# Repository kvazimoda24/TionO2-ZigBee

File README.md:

## README.md
Проект для подключения бризера Tion O2 к умному дому через протокол ZigBee

Отлаживалось на бризерах выпущенных в октябре 2020 года. На экземплярах выпущенных раньше или позже может использоваться другой дисплей или другая прошивка.

В бризере в качестве контроллера ЖК дисплея используется микросхема HOLTEK HT1622.<br>
Основная идея заключается в том, что мы цепляемся паралельно входу этой микросхемы и снифим данные, отправляемые в неё.<br>
Для управления замыкаем выводы кнопок панели управления бризера имитируя, таким образом, нажатия на них.<br>

Ядром проекта является микроконтроллер **ATmega328P**.<br>
Для работы по протоколу ZigBee используется модуль **E18-MS1-PCB**. Так же пробовал модуль **E18-MS1PA1-PCB**, но из-за встроенного усилителя он слишком много потребляет, и его не вытягивает встроенный блок питания бризера.

### Статус
При изменениях температуры или режима работы бризера, а также примерно каждые 20 минут на координатор отправляется текущий статус бризера.<br>
Посылка представляет JSON вида: `{"PWR":"1","APW":"1","OUT":"5","SPD":"3","HTE":"1","TMS":"0","HTT":"18"}`<br>
Параметры:<br>
**PWR** - работает бризер или в режиме standbuy (0 - standbuy, 1 - работает)<br>
**APW** - включён ли режим автоматического включения после сбоя питания. Если 1, то после подачи питания, если на момент сбоя бризер был включён, то бризер включится.<br>
**OUT** - температура входящего воздуха<br>
**SPD** - скорость работы вентилятора (от 1 до 4)<br>
**HTE** - включён ли подогрев воздуха<br>
**HTT** - до какой температуры подогревается входящий воздух<br>
**FLT** - осталось дней до замены фильтров<br>
**MNT** - минимально допустимая температура входящего воздуха<br>
**TIM** - текущее время (формат ЧЧММ)<br>
**TMS** - включён ли таймер включения/выключения<br>
**TME** - время включения (формат ЧЧММ)<br>
**TMD** - время выключения (формат ЧЧММ)<br>
**ERROR** - в случае, если бризер отобразил ошибку, то будет отправлен только этот параметр, в значении будет строка с ошибкой. Так же, в случае, если не удалось распознать данные на дисплее, то в значении будет пусто.

### Управление
Для управления необходимо отправить строку, содержащую одну или несколько команд.<br>
Строка состоит из названия параметра, разделителя, значения параметра. Разделителем является двоеточие ":".<br>
Можно отправить разом несколько параметров. В этом случае параметры должны отделаться друг от друга запятой ","<br>
Оканчиваться строка должна символом возврата каретки (код символа 0x0D).<br>
Максимальная длинна строки 127 символов.<br>
Параметры будут применяться в том же порядке, что и в отправленной команде.<br>
Если встречается ошибочный параметр, то дальнейший разбор строки прекращается.<br>

Пример строки: `PWR:1,SPD:2,HTE:1,HTT:17\r`

Сами параметры аналогичны тем, что перечислены в статусе, за исключением параметра FLT - изменение срока замены фильтров я не реализовывал, т.к. не увидел необходимости в этом.<br>
Так же, добавлена дополнительная команда EXS. Значение можно выставить любое число до 4 знаков, например 1.<br>
При получении этой команды контроллер проходит по всем настройкам бризера и отправляет их координатору ZigBee сети. Это нужно, чтобы получить текущие значения таймеров, текущего времени, срока службы фильтров и минимально допустимой температуры.<br>

На стороне координатора я использую проект zigbee2mqtt. В нём статус можно получить по адресу *zigbee2mqtt/device_id/action*
Строка с командами же отправляется по адресу *zigbee2mqtt/device_id/set/action* содержимое `PWR:1,SPD:2,HTE:1,HTT:17`

### Каталоги и файлы
**arduino** - проект в Arduino IDE версии 1.8.16 - сдесь код для контроллера ATmega328P<br>
**kicad** - проект в kiCAD версии 5.0.2 - схема платы, печатная плата и готовые герберы.<br>
**CC2530** - прошивки для ZigBee модулей<br>
**TION-O2_ZIGBEE.js** - файл описания устройства для zigbee2mqtt. Его надо положить в каталог data проекта zigbee2mqtt и прописать в файле configuration.yaml:
```
external_converters:
  - TION-O2_ZIGBEE.js
```
Прошивка для ZigBee модуля создана с помощью контруктора прошивок с сайта https://ptvo.info<br>
Вдохновлялся проектом https://hackaday.io/project/168959-let-me-control-you-hitachi-air-conditioner<br>

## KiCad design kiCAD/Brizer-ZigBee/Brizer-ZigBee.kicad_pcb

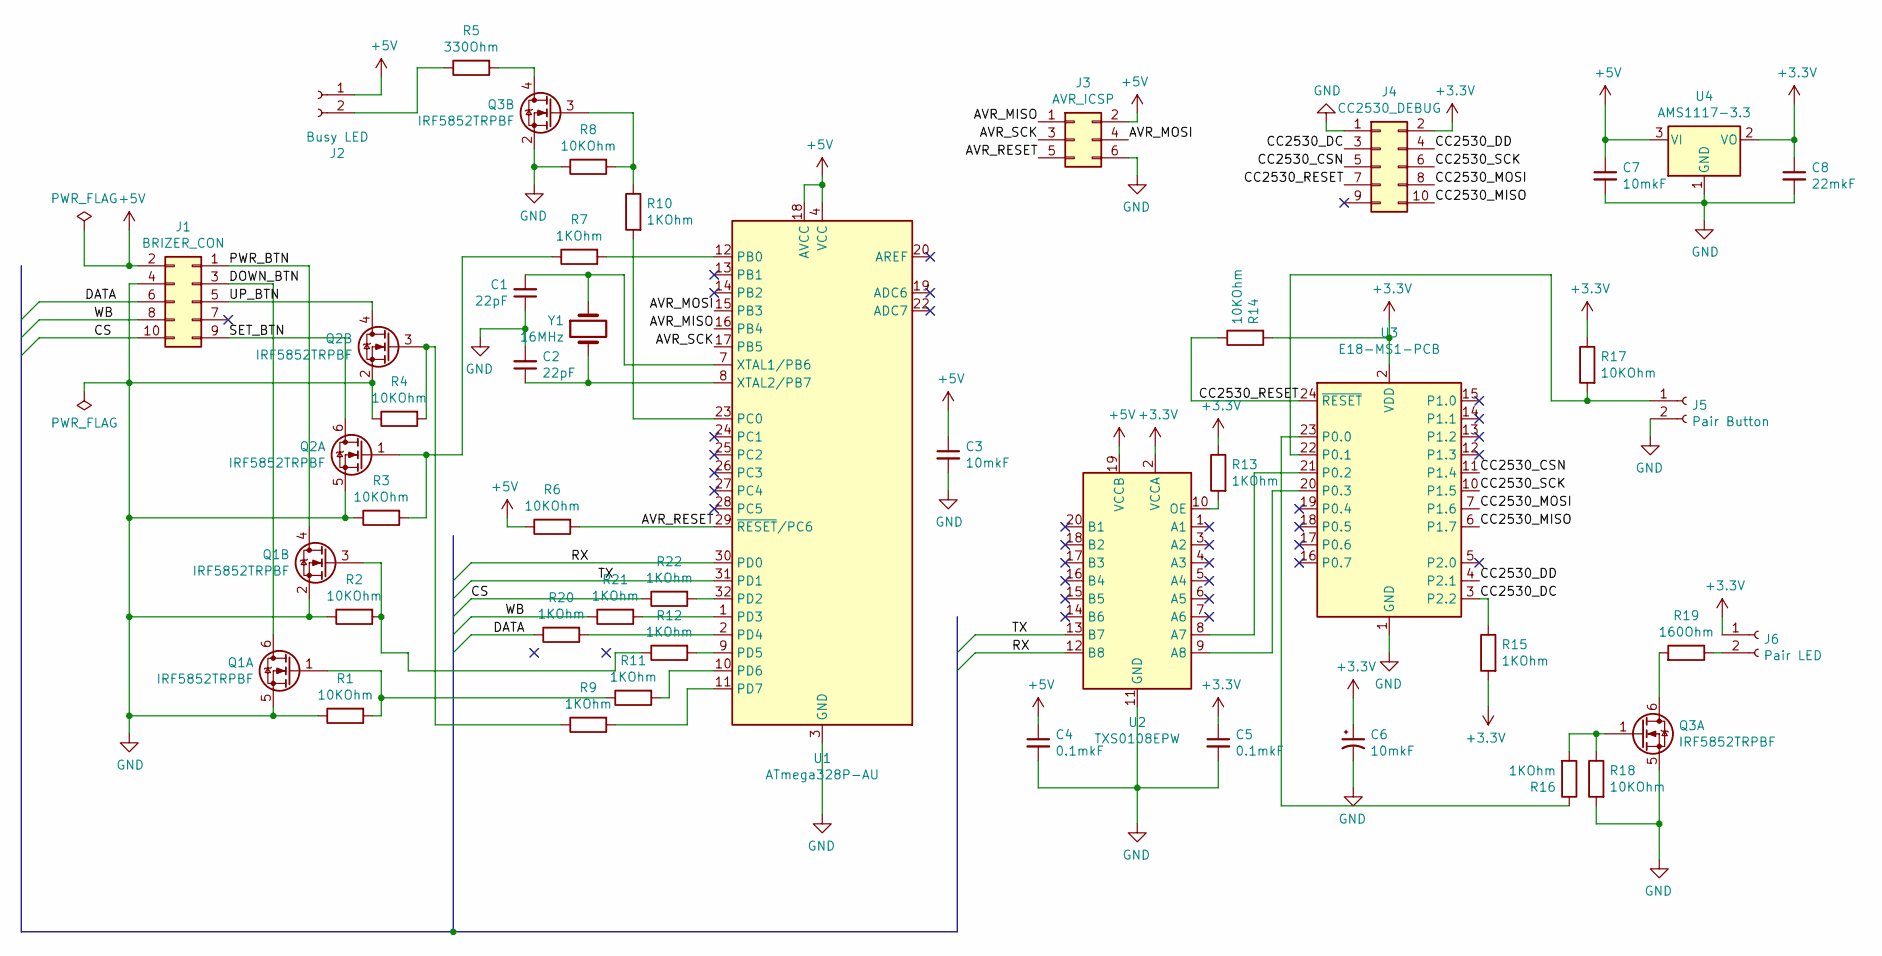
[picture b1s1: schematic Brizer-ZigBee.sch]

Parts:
C1, C2: 22pF; C_0805_2012Metric
C3, C7: 10mkF; C_0805_2012Metric
C4, C5: 0.1mkF; C_1206_3216Metric
C6: 10mkF; CP_EIA-3528-21_Kemet-B
C8: 22mkF; C_0805_2012Metric
J1: BRIZER_CON; IDC-Header_2x05_P2mm_Vertical
J2: Busy LED; PinHeader_1x02_P2.54mm_Vertical
J3: AVR_ICSP; PinHeader_2x03_P2.00mm_Vertical
J4: CC2530_DEBUG; PinHeader_2x05_P2.00mm_Vertical
J5: Pair Button; PinHeader_1x02_P2.54mm_Vertical
J6: Pair LED; PinHeader_1x02_P2.54mm_Vertical
Q1, Q2, Q3: IRF5852TRPBF; TSOP-6_1.65x3.05mm_P0.95mm
R1, R2, R3, R4, R6, R8, R14, R17, R18: 10KOhm; R_0805_2012Metric
R5: 330Ohm; R_0805_2012Metric
R7, R9, R10, R11, R12, R13, R15, R16, R20, R21, R22: 1KOhm; R_0805_2012Metric
R19: 160Ohm; R_0805_2012Metric
U1: ATmega328P-AU; TQFP-32_7x7mm_P0.8mm
U2: TXS0108EPW; TSSOP-20_4.4x6.5mm_P0.65mm
U3: E18-MS1-PCB; E18-MS1PA1-PCB
U4: AMS1117-3.3; SOT-223-3_TabPin2
Y1: 16MHz; Crystal_SMD_HC49-SD

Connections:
+3V3: C5.1, C6.1, C8.1, J4.2, J6.1, R13.1, R14.2, R15.2, R17.1, U2.2 (VCCA), U3.2 (VDD), U4.2 (VO)
+5V: C3.1, C4.1, C7.1, J1.2, J2.1, J3.2, R6.1, U1.4 (VCC), U1.6 (VCC), U1.18 (AVCC), U2.19 (VCCB), U4.3 (VI)
/AVR_MISO: J3.1, U1.16 (PB4)
/AVR_MOSI: J3.4, U1.15 (PB3)
/AVR_RESET: J3.5, R6.2, U1.29 (~RESET~/PC6)
/AVR_SCK: J3.3, U1.17 (PB5)
/CC2530_CSN: J4.5, U3.11 (P1.4)
/CC2530_DC: J4.3, R15.1, U3.3 (P2.2)
/CC2530_DD: J4.4, U3.4 (P2.1)
/CC2530_MISO: J4.10, U3.6 (P1.7)
/CC2530_MOSI: J4.8, U3.7 (P1.6)
/CC2530_RESET: J4.7, R14.1, U3.24 (~RESET)
/CC2530_SCK: J4.6, U3.10 (P1.5)
/CS: J1.10, R22.1
/DATA: J1.6, R20.1
/DOWN_BTN: J1.3, Q1.6 (D)
/PWR_BTN: J1.1, Q1.4 (D)
/RX: U1.30 (PD0), U2.12 (B8)
/SET_BTN: J1.9, Q2.6 (D)
/TX: U1.31 (PD1), U2.13 (B7)
/UP_BTN: J1.5, Q2.4 (D)
/WB: J1.8, R21.1
GND: C1.1, C2.2, C3.2, C4.2, C5.2, C6.2, C7.2, C8.2, J1.4, J3.6, J4.1, J5.2, Q1.2 (S), Q1.5 (S), Q2.2 (S), Q2.5 (S), Q3.2 (S), Q3.5 (S), R1.1, R2.1, R3.1, R4.1, R8.1, R18.2, U1.3 (GND), U1.5 (GND), U1.21 (GND), U2.11 (GND), U3.1 (GND), U4.1 (GND)
unnamed: C1.2, U1.7 (XTAL1/PB6), Y1.1
unnamed: C2.1, U1.8 (XTAL2/PB7), Y1.2
unnamed: J2.2, R5.1
unnamed: J5.1, R17.2, U3.22 (P0.1)
unnamed: J6.2, R19.1
unnamed: Q1.1 (G), R1.2, R11.1
unnamed: Q1.3 (G), R2.2, R12.1
unnamed: Q2.1 (G), R3.2, R7.1
unnamed: Q2.3 (G), R4.2, R9.1
unnamed: Q3.1 (G), R16.2, R18.1
unnamed: Q3.3 (G), R8.2, R10.1
unnamed: Q3.4 (D), R5.2
unnamed: Q3.6 (D), R19.2
unnamed: R7.2, U1.12 (PB0)
unnamed: R9.2, U1.11 (PD7)
unnamed: R10.2, U1.23 (PC0)
unnamed: R11.2, U1.10 (PD6)
unnamed: R12.2, U1.9 (PD5)
unnamed: R13.2, U2.10 (OE)
unnamed: R16.1, U3.23 (P0.0)
unnamed: R20.2, U1.2 (PD4)
unnamed: R21.2, U1.1 (PD3)
unnamed: R22.2, U1.32 (PD2)
unnamed: U2.8 (A7), U3.21 (P0.2)
unnamed: U2.9 (A8), U3.20 (P0.3)

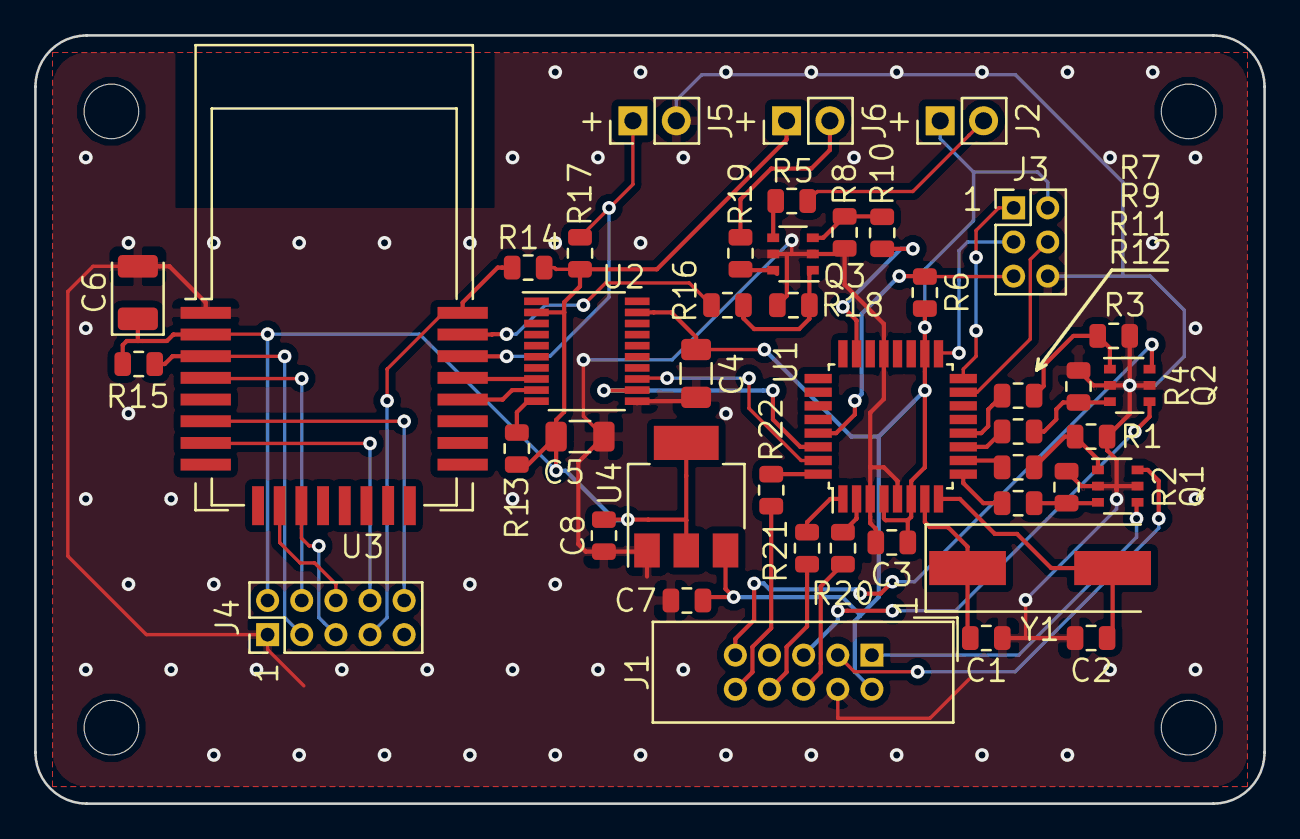
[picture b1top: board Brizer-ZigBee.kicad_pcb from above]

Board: 2 copper layers, 72.0 x 45.0 mm, 44 parts (0 on the bottom side), 48 nets.

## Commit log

2021-10-19 Load project
2021-10-19 Add ZigBee firmwares and Readme
2021-10-19 Add README with Fuse bits for ATmega
